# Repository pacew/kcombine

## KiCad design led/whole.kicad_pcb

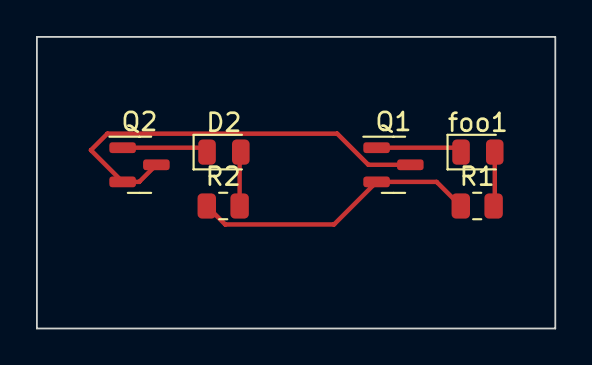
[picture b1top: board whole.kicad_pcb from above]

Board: 2 copper layers, 28.8 x 16.2 mm, 6 parts (0 on the bottom side), 6 nets.

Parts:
D2: LED; LED_0805_2012Metric
Q1, Q2: Q_NMOS_DGS; SOT-23
R1, R2: R; R_0805_2012Metric
foo1: LED; LED_0805_2012Metric

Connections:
+3V3: Q1.2 (G), R1.1, R2.1
/whole1/switched: Q1.1 (D), foo1.1 (K)
/whole2/switched: D2.1 (K), Q2.1 (D)
GND: Q1.3 (S), Q2.2 (G), Q2.3 (S)
unnamed: D2.2 (A), R2.2
unnamed: R1.2, foo1.2 (A)

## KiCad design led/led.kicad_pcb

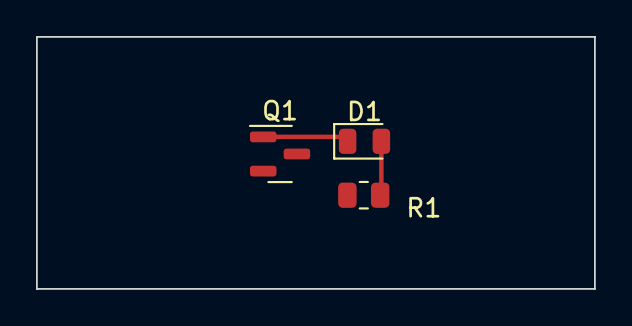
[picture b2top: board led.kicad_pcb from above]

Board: 2 copper layers, 31.0 x 14.0 mm, 3 parts (0 on the bottom side), 2 nets.

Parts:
D1: LED; LED_0805_2012Metric
Q1: Q_NMOS_DGS; SOT-23
R1: R; R_0805_2012Metric

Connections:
/led/switched: D1.1 (K), Q1.1 (D)
unnamed: D1.2 (A), R1.2

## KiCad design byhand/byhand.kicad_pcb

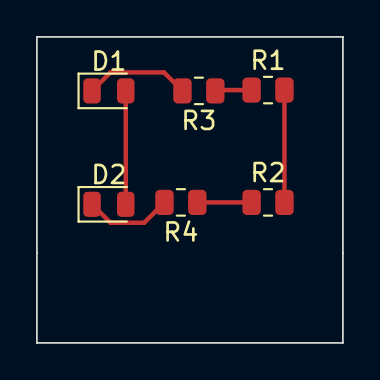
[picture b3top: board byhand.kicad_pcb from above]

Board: 2 copper layers, 17.0 x 17.0 mm, 6 parts (0 on the bottom side), 6 nets.

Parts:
D1, D2: LED; LED_0805_2012Metric
R1, R2, R3, R4: R; R_0805_2012Metric

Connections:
+3V3: D1.2 (A), D2.2 (A)
/LED_C: D2.1 (K), R4.2
/curlimit1/foo: R1.1, R3.1
/curlimit2/foo: R2.1, R4.1
/test: D1.1 (K), R3.2
ground: R1.2, R2.2

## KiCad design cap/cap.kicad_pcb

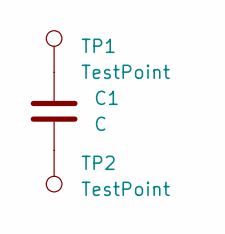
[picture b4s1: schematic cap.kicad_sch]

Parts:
C1: C; C_0805_2012Metric
TP1, TP2: TestPoint; TestPoint_Pad_D1.0mm

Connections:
unnamed: C1.1, TP1.1
unnamed: C1.2, TP2.1

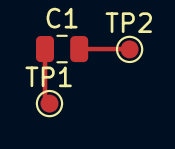
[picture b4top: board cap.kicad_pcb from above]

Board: 2 copper layers, 3 parts (0 on the bottom side), 2 nets.

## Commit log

2020-12-31 start
2020-12-31 examples
2020-12-31 combine
2020-12-31 tweak
2021-01-01 lisp
2021-01-02 progress
2021-01-02 parents
2021-01-03 uuid
2021-01-03 sexp
2021-01-03 works some
2021-01-03 symbol_instances
2021-01-03 nice
2021-01-04 tweaks
2021-01-07 cleanup
2021-01-08 cleanup sch
2021-01-09 iter
2021-01-09 subclass
2021-01-10 baseline
2021-01-10 files
2021-01-30 cleanups
2021-01-30 quotes
2021-01-30 print
